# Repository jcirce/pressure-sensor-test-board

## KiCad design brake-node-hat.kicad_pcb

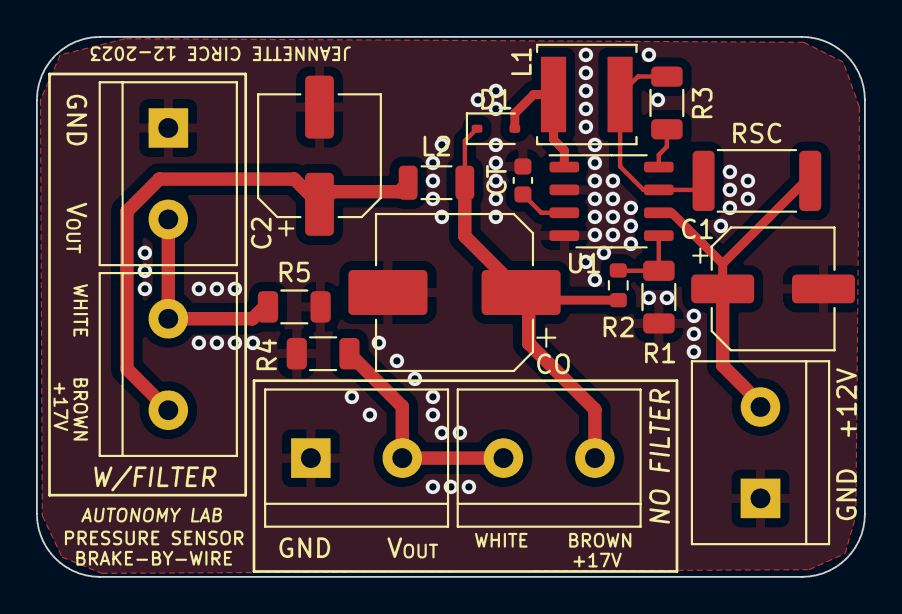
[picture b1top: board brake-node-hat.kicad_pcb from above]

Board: 2 copper layers, 46.0 x 30.0 mm, 19 parts (0 on the bottom side), 11 nets.

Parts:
C1: 100 uF; CP_Elec_6.3x5.4
C2: 100 uF; CP_Elec_6.3x7.7
CO: 330 uF; CP_Elec_8x10.5
CT: 140 pF; C_0603_1608Metric
D1: 1N5819; D_SOD-323
J1, J4, J5, J6, J7: Screw_Terminal_01x02; TerminalBlock_bornier-2_P5.08mm
L1: 300uH; L_Changjiang_FNR5040S
L2: 1.0uH; L_1206_3216Metric
R1: 3.4k Ohm; R_1206_3216Metric
R2: 47k Ohm; R_0603_1608Metric
R3: 180; R_1206_3216Metric
R4, R5: 220; R_1206_3216Metric
RSC: 0.43 Ohm; R_2512_6332Metric
U1: SOP-8_3.9x4.9mm_P1.27mm

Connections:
+12V: C1.1, J1.2, RSC.2, U1.6 (Vcc)
GND: C1.2, C2.2, CO.2, CT.2, J1.1, J5.1, J7.1, R1.1, R4.2, R5.2, U1.2 (Switch_Emitter), U1.4 (GND)
unnamed: D1.2 (A), L1.1, U1.1 (Switch_Collector)
unnamed: J4.1, J5.2, R4.1
unnamed: J6.1, J7.2, R5.1
unnamed: R1.2, R2.1, U1.5 (Comparator_Inverting_Input)
unnamed: R3.2, U1.8 (Driver_Collector)
unnamed: L1.2, R3.1, RSC.1, U1.7 (I_PEAK_Sense)
unnamed: CT.1, U1.3 (Timing_Capacitor)
VD: CO.1, D1.1 (K), J4.2, L2.1, R2.2
VDD: C2.1, J6.2, L2.2

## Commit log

2023-12-01 layout/screenprint done
2024-01-22 adding gerber zip
